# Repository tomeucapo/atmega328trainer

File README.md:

# ATmega328P Weather Station

Firmware and KiCad designs for an ATmega328P weather station and its battery-powered LoRa sensor nodes. The master reads local wind, rain and temperature sensors, displays measurements on an OLED, stores records in I²C EEPROM, and receives remote BME280 readings over LoRa.

The original trainer board includes an optocoupled input for pulse sensors, including 24 V anemometers, and an FT232 USB-to-serial interface.

| Weather station board | IO Expansion board |
| --- | --- |
|  |  |

[PCB project page](https://www.pcbway.com/project/shareproject/Anemometer_with_ATMega128P_fbefd825.html) · [Master schematic (PDF)](schematic/anemometre.pdf) · [IOExtension schematic (PDF)](schematic/IOExtension/IOExtension/IOExtension.pdf) · [Local LoRa/BME280 schematic (PDF)](schematic/lora_bme280_local/lora_bme280_local/lora_bme280_local.pdf)

## Features

- Wind speed from an anemometer and rainfall counting.
- Local temperature from a DS18B20 and indoor temperature, humidity and pressure from a BME280.
- SSD1306 OLED with text and temperature-graph views.
- MCP23017 I/O expander, including an external LED and view button.
- I²C EEPROM logging and weather forecast calculations.
- SX1276/78 LoRa support for up to two remote BME280 nodes.
- Separate firmware target for the low-power remote node.
- Optional BME280 and LoRa devices are detected at startup; if the LoRa module is absent, the master reports it over UART and continues with local functions.

## Hardware

### Master board

| ATmega328P pin | Function |
| --- | --- |
| PB0 | Anemometer input capture (ICP1) |
| PB1 | Rain gauge input (PCINT1) |
| PB2 | DS18B20 1-Wire data; use a 4.7 kΩ pull-up |
| PB3/PB4/PB5 | SPI MOSI/MISO/SCK for the LoRa module |
| PC4/PC5 | I²C SDA/SCL, 100 kHz |
| PD0/PD1 | UART RX/TX, shared with the onboard FT232 |
| PD2/PD3 | LoRa chip select/reset |
| PD6 | Status LED |

The I²C bus is shared by the MCP23017 (`0x20`), SSD1306 (`0x3C`), EEPROM (`0x54`) and BME280 (`0x76`). PB2 is also the ATmega328P SPI `SS` pin, so the firmware suspends SPI while it communicates with the DS18B20 and restores SPI master mode afterward.

The master MCU operates at 8 MHz. The RFM95W/Ra-02 LoRa module is a **3.3 V device**; use a suitable 3.3 V regulator and level shifting between it and a 5 V MCU. Keep the module's chip-select pulled high so ISP programming does not select the radio.

### LoRa remote node

The remote uses an ATmega328P at 3.3 V / 8 MHz, a BME280 and an SX127x radio. It transmits approximately every 64 seconds and sleeps between transmissions. Build node 1 by default; node 2 starts with a 32-second offset to reduce collisions. The master marks a node offline after 180 seconds without a packet.

For remote battery measurement, connect VIN to PC0/ADC0 through a divider: VIN—470 kΩ—PC0—330 kΩ—GND, with 100 nF from PC0 to GND. PC0 is not connected on the current remote PCB, so the divider must be wired to the ATmega328P pin 23. The reported voltage assumes a 3.3 V ADC reference and these resistor values; calibrate for best accuracy.

## Build

Install CMake and the AVR toolchain (`gcc-avr`, `avr-libc`; `binutils-avr` may be a separate package on your system). The master and remote are separate CMake projects.

### Master firmware

From the repository root:

```sh
cmake -S src -B src/build
cmake --build src/build
```

The build creates `src/build/firmware.elf` and `src/build/firmware.hex`. If CMake cached a host compiler instead of `avr-gcc`, use a fresh build directory and configure again.

### LoRa remote firmware

```sh
cmake -S src/lora_remote -B src/lora_remote/build
cmake --build src/lora_remote/build
```

To build node 2, use a separate build directory:

```sh
cmake -S src/lora_remote -B src/lora_remote/build_node2 -DLORA_NODE_ID=2
cmake --build src/lora_remote/build_node2
```

The remote's optional UART diagnostics are disabled by default. Enable them with `-DLORA_DEBUG_UART=ON` in a separate build directory; output is 9600 baud, 8N1, on PD1/TXD and uses 3.3 V logic levels.

```sh
cmake -S src/lora_remote -B src/lora_remote/build_debug -DLORA_DEBUG_UART=ON
cmake --build src/lora_remote/build_debug
```

The remote build creates `firmware_remote.elf` and `firmware_remote.hex` in its selected build directory. For UART diagnostics, connect a 3.3 V USB-to-serial adapter's RX to PD1/TXD and connect GND; the remote only transmits debug output.

Both projects provide a `flash` target that invokes `avrdude` with the `dragon_isp` programmer. Select the appropriate build directory and connect the programmer before running it:

```sh
cmake --build src/build --target flash
cmake --build src/lora_remote/build --target flash
```

## Master serial interface

The master UART is 9600 baud, 8N1 on PD0/PD1, exposed through the onboard FT232. Commands are terminated by CR or LF.

| Command | Purpose |
| --- | --- |
| `@GET_ANEMO` | Read wind speed |
| `@GET_RAIN` | Read rain-tip count and rainfall |
| `@RESET_RAIN` | Reset the rain counter |
| `@GET_TEMP` | Read the DS18B20 temperature |
| `@GET_BME` | Read the latest indoor BME280 data |
| `@GET_EXT` | Read remote node 1 status (alias for `@GET_EXT1`) |
| `@GET_EXT1`, `@GET_EXT2` | Read the selected remote node status |
| `@VIEW` | Toggle OLED text/graph view |
| `@DUMP` | Dump logged EEPROM records |
| `@FORECAST` | Print the current forecast |
| `@MCP_ON <pin>`, `@MCP_OFF <pin>` | Set an MCP23017 output; use `A0`–`A6` or `B0`–`B7` (port A is the default) |

The OLED text view shows both the exterior DS18B20 and indoor BME280 temperatures. `src/test.py` is an older host-side script and still uses legacy `@STAT_*` command names.

## Repository layout

- `src/weatherstation/` — master firmware and shared sensor, display, I²C, SPI, EEPROM and LoRa drivers.
- `src/lora_remote/` — battery-powered remote-node firmware.
- `schematic/` — KiCad schematics and PCB designs for the master and LoRa nodes.

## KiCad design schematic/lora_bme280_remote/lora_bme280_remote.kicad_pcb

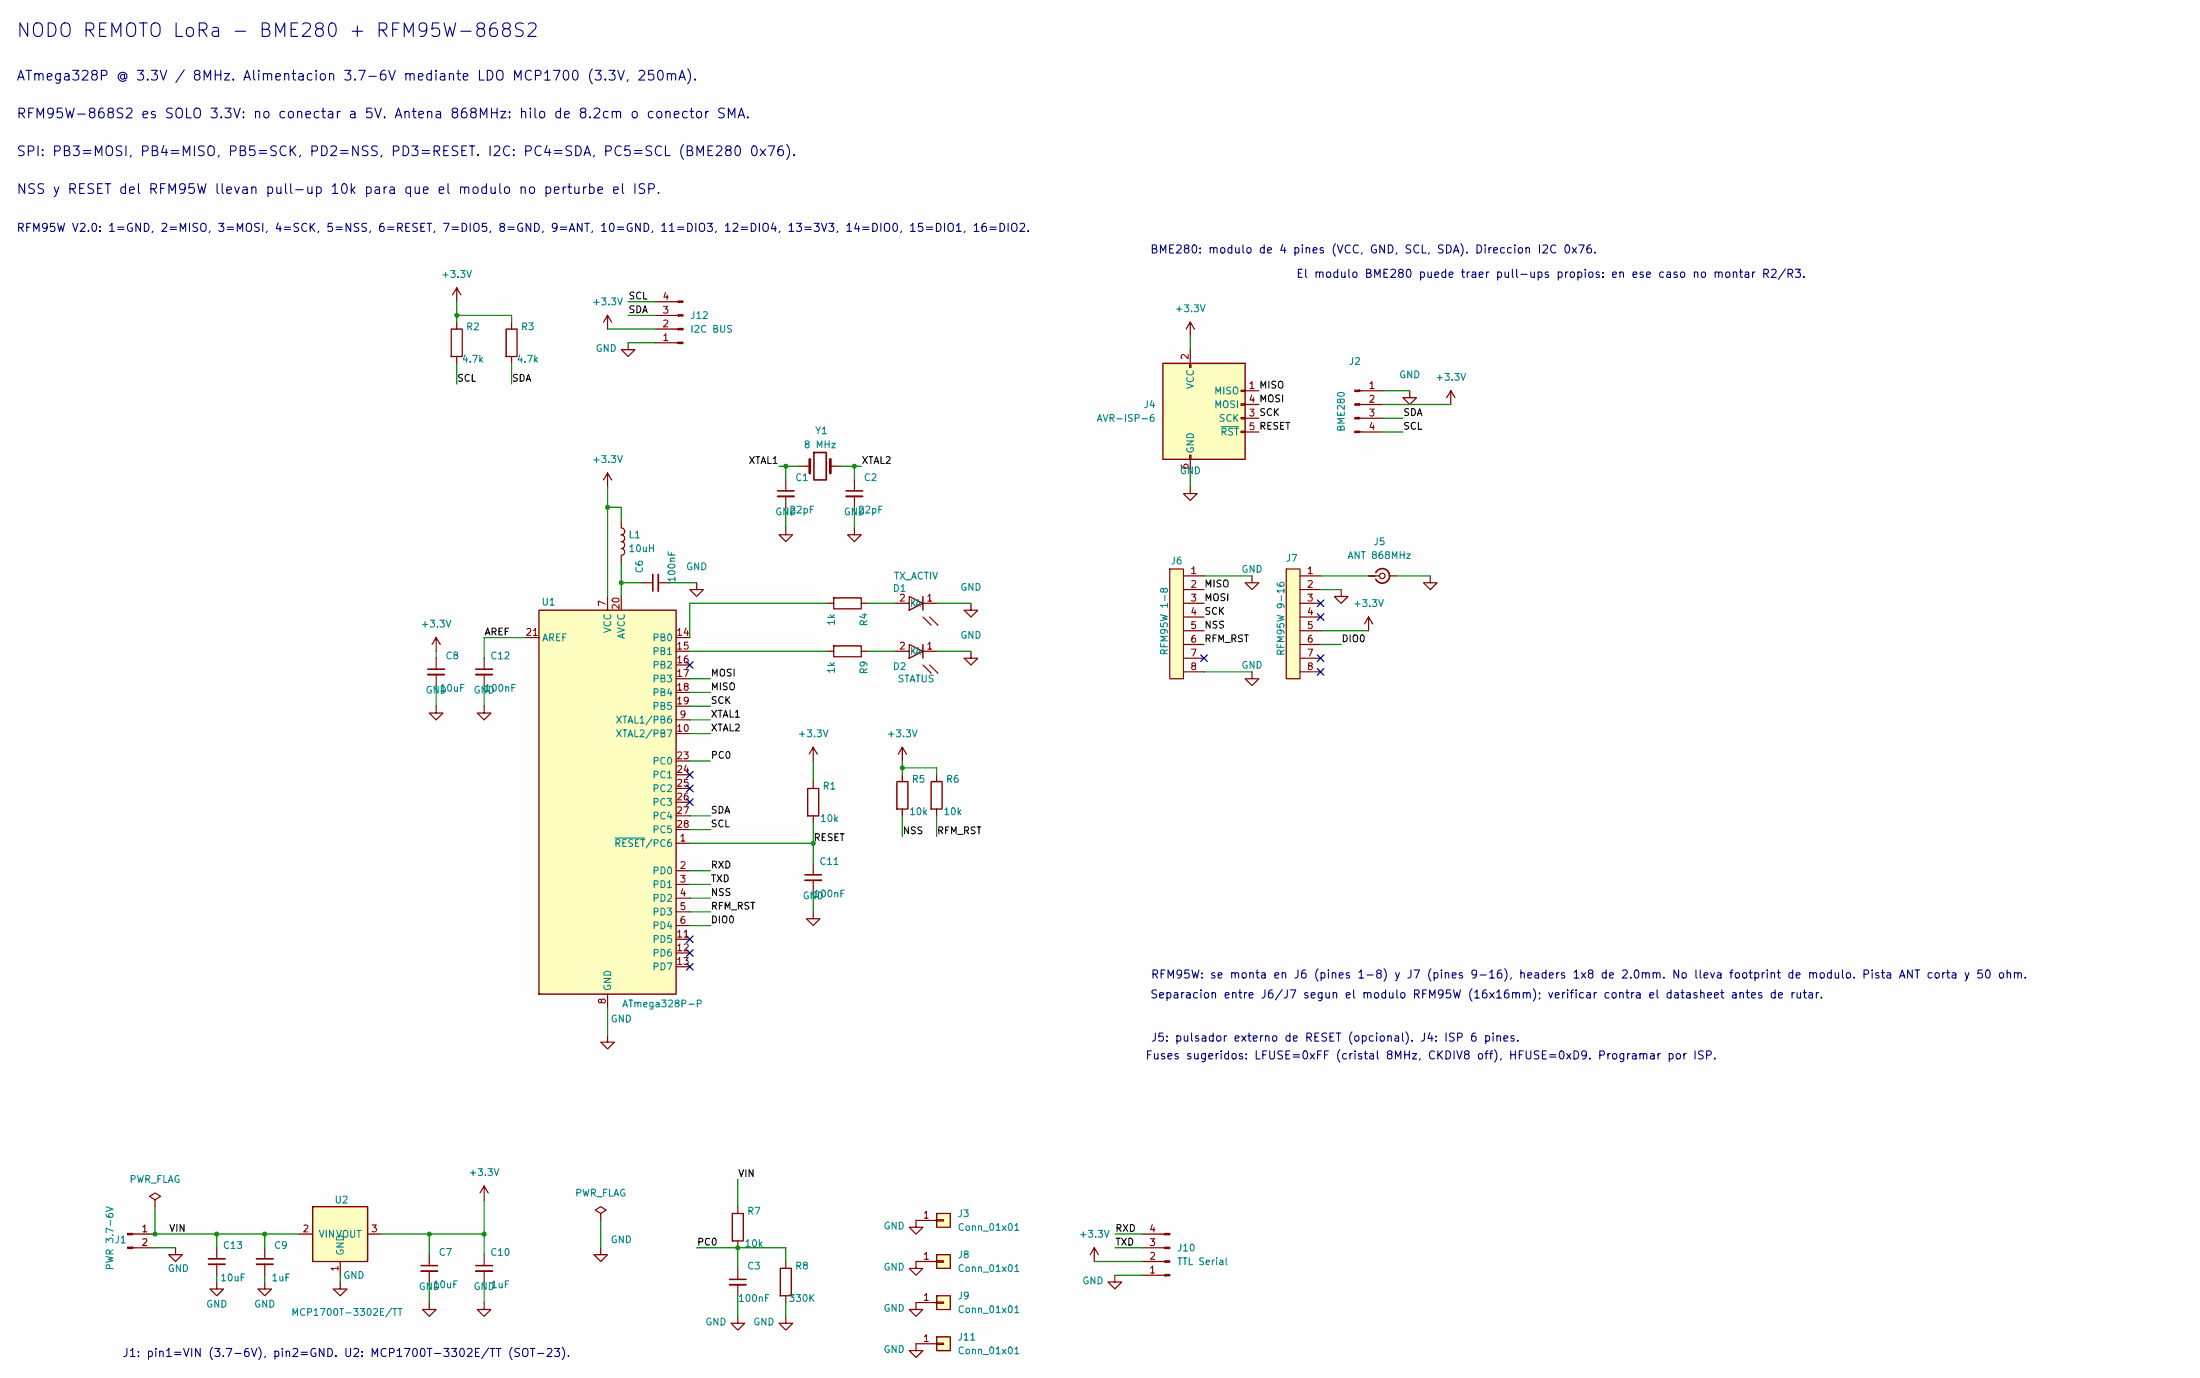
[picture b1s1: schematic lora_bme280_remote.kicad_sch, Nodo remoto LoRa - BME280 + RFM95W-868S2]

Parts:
C1, C2: 22pF; C_Disc_D4.3mm_W1.9mm_P5.00mm
C3, C6, C11, C12: 100nF; C_Disc_D7.0mm_W2.5mm_P5.00mm
C7, C13: 10uF; C_0805_2012Metric
C8: 10uF; C_Disc_D7.0mm_W2.5mm_P5.00mm
C9, C10: 1uF; C_0805_2012Metric
D1: TX_ACTIV; LED_D3.0mm
D2: STATUS; LED_D3.0mm
J1: PWR 3.7-6V; JST_EH_B2B-EH-A_1x02_P2.50mm_Vertical
J2: BME280; PinHeader_1x04_P2.00mm_Vertical
J3, J8, J9, J11: Conn_01x01; MountingHole_3mm_Pad
J4: AVR-ISP-6; IDC-Header_2x03_P2.54mm_Vertical; MPN 75869-131LF; Farnell 2293757
J5: ANT 868MHz; SMA_Amphenol_132134_Vertical
J6: RFM95W 1-8; PinHeader_1x08_P2.00mm_Vertical
J7: RFM95W 9-16; PinHeader_1x08_P2.00mm_Vertical
J10: TTL Serial; PinHeader_1x04_P2.54mm_Vertical
J12: I2C BUS; PinHeader_1x04_P2.54mm_Vertical
L1: 10uH; L_Axial_L5.3mm_D2.2mm_P10.16mm_Horizontal_Vishay_IM-1; MPN 77F100K-TR-RC; Farnell 2924990
R1, R5, R6, R7: 10k; R_Axial_DIN0204_L3.6mm_D1.6mm_P7.62mm_Horizontal
R2, R3: 4.7k; R_Axial_DIN0204_L3.6mm_D1.6mm_P7.62mm_Horizontal
R4, R9: 1k; R_Axial_DIN0204_L3.6mm_D1.6mm_P7.62mm_Horizontal
R8: 330K; R_Axial_DIN0204_L3.6mm_D1.6mm_P7.62mm_Horizontal
U1: ATmega328P-P; DIP-28_W7.62mm; MPN ATMEGA328P-PU; Farnell 1715487
U2: MCP1700T-3302E/TT; SOT-23
Y1: 8 MHz; Crystal_HC49-U_Vertical

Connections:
+3.3V: C7.1, C8.1, C10.1, J2.2, J4.2 (VCC), J7.5, J10.2, J12.2, L1.1, R1.1, R2.1, R3.1, R5.1, R6.1, U1.7 (VCC), U2.3 (VOUT)
/AREF: C12.1, U1.21 (AREF)
/DIO0: J7.6, U1.6 (PD4)
/MISO: J4.1 (MISO), J6.2, U1.18 (PB4)
/MOSI: J4.4 (MOSI), J6.3, U1.17 (PB3)
/NSS: J6.5, R5.2, U1.4 (PD2)
/PC0: C3.1, R7.2, R8.1, U1.23 (PC0)
/RESET: C11.1, J4.5 (~RST), R1.2, U1.1 (~RESET/PC6)
/RFM_RST: J6.6, R6.2, U1.5 (PD3)
/RXD: J10.4, U1.2 (PD0)
/SCK: J4.3 (SCK), J6.4, U1.19 (PB5)
/SCL: J2.4, J12.4, R2.2, U1.28 (PC5)
/SDA: J2.3, J12.3, R3.2, U1.27 (PC4)
/TXD: J10.3, U1.3 (PD1)
/VIN: C9.1, C13.1, J1.1, R7.1, U2.2 (VIN)
/XTAL1: C1.1, U1.9 (XTAL1/PB6), Y1.1
/XTAL2: C2.1, U1.10 (XTAL2/PB7), Y1.2
GND: C1.2, C2.2, C3.2, C6.2, C7.2, C8.2, C9.2, C10.2, C11.2, C12.2, C13.2, D1.1 (K), D2.1 (K), J1.2, J2.1, J3.1, J4.6 (GND), J5.2 (Ext), J6.1, J6.8, J7.2, J8.1, J9.1, J10.1, J11.1, J12.1, R8.2, U1.8 (GND), U1.22 (GND), U2.1 (GND)
unnamed: D1.2 (A), R4.1
unnamed: D2.2 (A), R9.1
unnamed: J5.1 (In), J7.1
unnamed: C6.1, L1.2, U1.20 (AVCC)
unnamed: R4.2, U1.14 (PB0)
unnamed: R9.2, U1.15 (PB1)

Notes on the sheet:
ATmega328P @ 3.3V / 8MHz. Alimentacion 3.7-6V mediante LDO MCP1700 (3.3V, 250mA).
RFM95W-868S2 es SOLO 3.3V: no conectar a 5V. Antena 868MHz: hilo de 8.2cm o conector SMA.
BME280: modulo de 4 pines (VCC, GND, SCL, SDA). Direccion I2C 0x76.
NODO REMOTO LoRa - BME280 + RFM95W-868S2
RFM95W: se monta en J6 (pines 1-8) y J7 (pines 9-16), headers 1x8 de 2.0mm. No lleva footprint de modulo. Pista ANT corta y 50 ohm.
SPI: PB3=MOSI, PB4=MISO, PB5=SCK, PD2=NSS, PD3=RESET. I2C: PC4=SDA, PC5=SCL (BME280 0x76).
J5: pulsador externo de RESET (opcional). J4: ISP 6 pines.
Separacion entre J6/J7 segun el modulo RFM95W (16x16mm); verificar contra el datasheet antes de rutar.
Fuses sugeridos: LFUSE=0xFF (cristal 8MHz, CKDIV8 off), HFUSE=0xD9. Programar por ISP.
El modulo BME280 puede traer pull-ups propios: en ese caso no montar R2/R3.
J1: pin1=VIN (3.7-6V), pin2=GND. U2: MCP1700T-3302E/TT (SOT-23).
RFM95W V2.0: 1=GND, 2=MISO, 3=MOSI, 4=SCK, 5=NSS, 6=RESET, 7=DIO5, 8=GND, 9=ANT, 10=GND, 11=DIO3, 12=DIO4, 13=3V3, 14=DIO0, 15=DIO1, 16=DIO2.
NSS y RESET del RFM95W llevan pull-up 10k para que el modulo no perturbe el ISP.

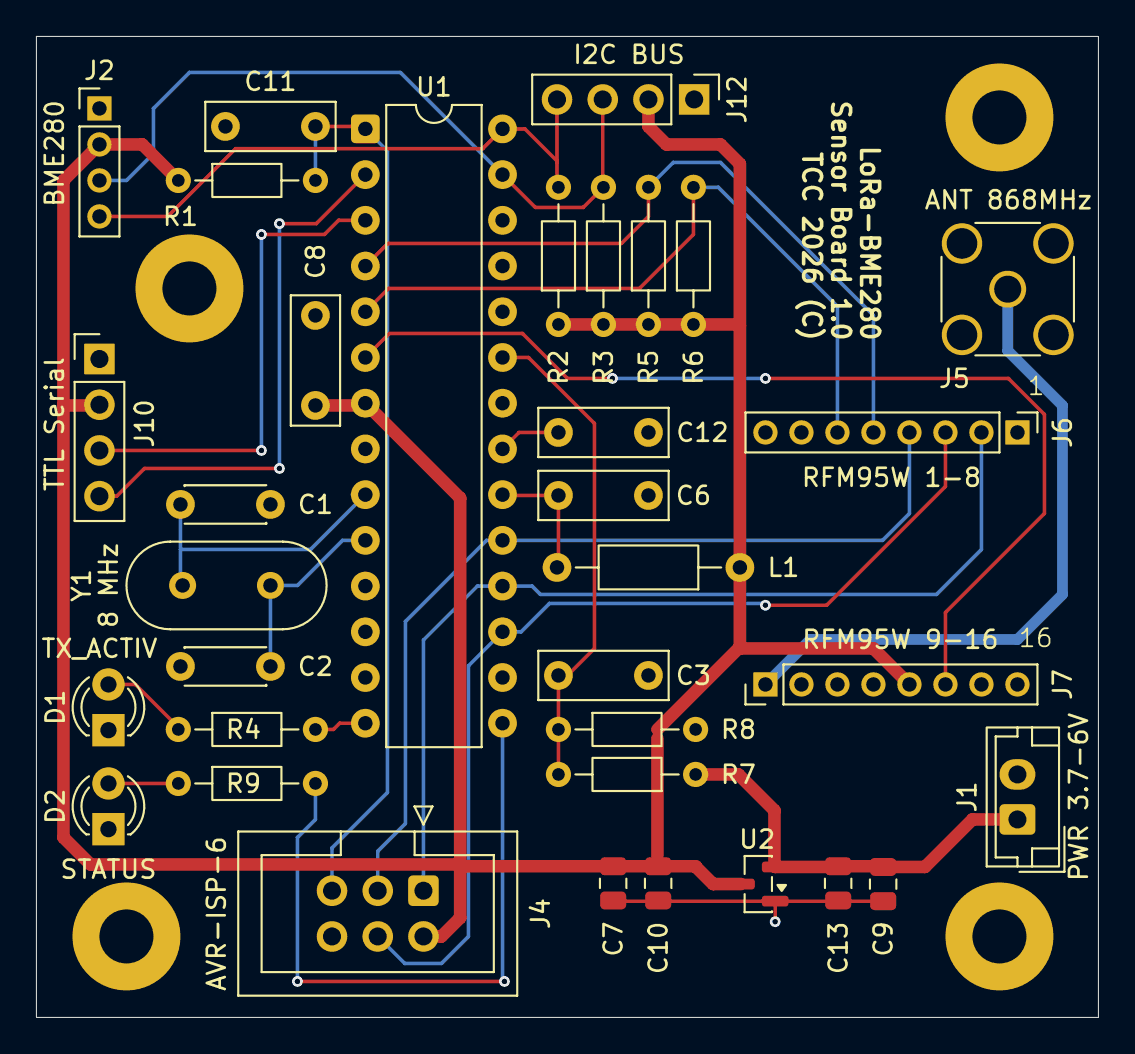
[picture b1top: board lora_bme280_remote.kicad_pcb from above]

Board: 2 copper layers, 59.0 x 54.5 mm, 38 parts (0 on the bottom side), 24 nets.

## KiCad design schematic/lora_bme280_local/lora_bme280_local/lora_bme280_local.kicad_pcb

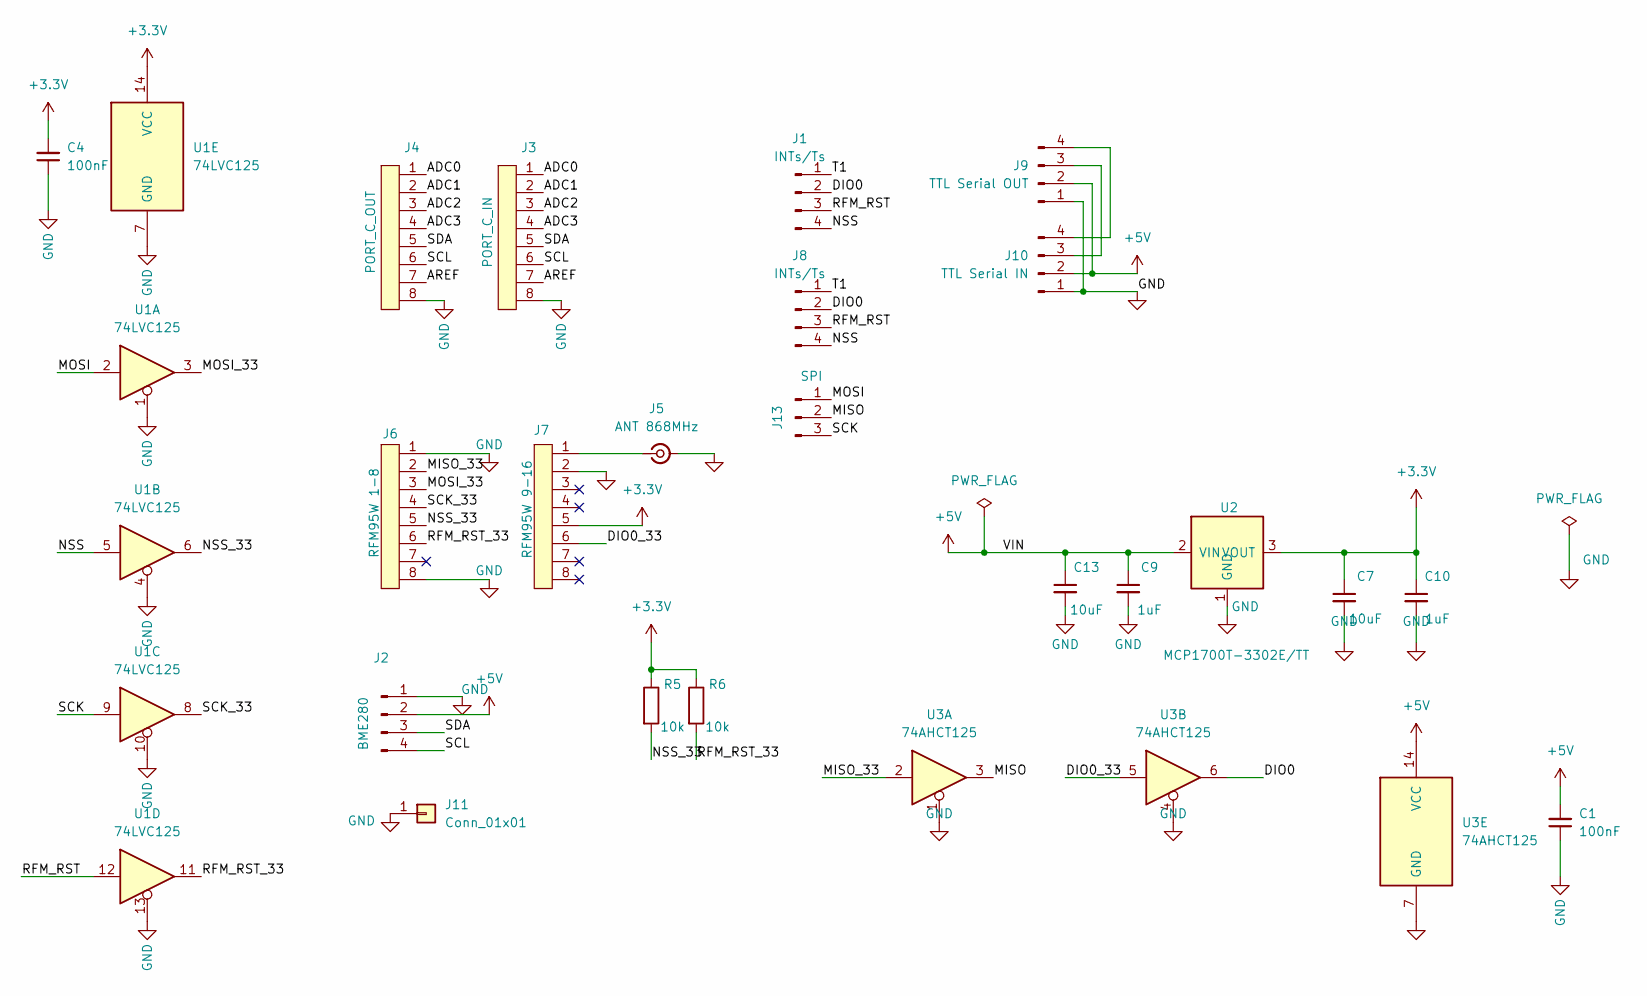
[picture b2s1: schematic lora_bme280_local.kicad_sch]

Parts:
C1: 100nF; C_Disc_D7.0mm_W2.5mm_P5.00mm; MPN CK05BX104K; Farnell 1740547
C4: 100nF; C_0805_2012Metric_Pad1.18x1.45mm_HandSolder; MPN CK05BX104K; Farnell 1740547
C7, C13: 10uF; C_0805_2012Metric
C9, C10: 1uF; C_0805_2012Metric
J1, J8: INTs/Ts; PinHeader_1x04_P2.54mm_Vertical
J2: BME280; JST_PH_B4B-PH-K_1x04_P2.00mm_Vertical
J3: PORT_C_IN; PinHeader_1x08_P2.54mm_Vertical
J4: PORT_C_OUT; PinHeader_1x08_P2.54mm_Vertical
J5: ANT 868MHz; SMA_Amphenol_132134-11_Vertical
J6: RFM95W 1-8; PinHeader_1x08_P2.00mm_Vertical
J7: RFM95W 9-16; PinHeader_1x08_P2.00mm_Vertical
J9: TTL Serial OUT; PinHeader_1x04_P2.54mm_Vertical
J10: TTL Serial IN; PinHeader_1x04_P2.54mm_Vertical
J11: Conn_01x01; MountingHole_3mm_Pad
J13: SPI; PinHeader_1x03_P2.54mm_Vertical
R5, R6: 10k; R_Axial_DIN0204_L3.6mm_D1.6mm_P7.62mm_Horizontal
U1: 74LVC125; TSSOP-14_4.4x5mm_P0.65mm
U2: MCP1700T-3302E/TT; SOT-23
U3: 74AHCT125; DIP-14_W7.62mm

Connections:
+3.3V: C4.2, C7.1, C10.1, J7.5, R5.1, R6.1, U1.14 (VCC), U2.3 (VOUT)
+5V: C1.2, C9.1, C13.1, J2.2, J9.2, J10.2, U2.2 (VIN), U3.14 (VCC)
/ADC0: J3.1, J4.1
/ADC1: J3.2, J4.2
/ADC2: J3.3, J4.3
/ADC3: J3.4, J4.4
/AREF: J3.7, J4.7
/DIO0: J1.2, J8.2, U3.6
/DIO0_33: J7.6, U3.5
/MISO: J13.2, U3.3
/MISO_33: J6.2, U3.2
/MOSI: J13.1, U1.2
/MOSI_33: J6.3, U1.3
/NSS: J1.4, J8.4, U1.5
/NSS_33: J6.5, R5.2, U1.6
/RFM_RST: J1.3, J8.3, U1.12
/RFM_RST_33: J6.6, R6.2, U1.11
/SCK: J13.3, U1.9
/SCK_33: J6.4, U1.8
/SCL: J2.4, J3.6, J4.6
/SDA: J2.3, J3.5, J4.5
/T1: J1.1, J8.1
GND: C1.1, C4.1, C7.2, C9.2, C10.2, C13.2, J2.1, J3.8, J4.8, J5.2 (Ext), J6.1, J6.8, J7.2, J9.1, J10.1, J11.1, U1.1, U1.4, U1.7 (GND), U1.10, U1.13, U2.1 (GND), U3.1, U3.4, U3.7 (GND)
unnamed: J5.1 (In), J7.1
unnamed: J9.3, J10.3
unnamed: J9.4, J10.4

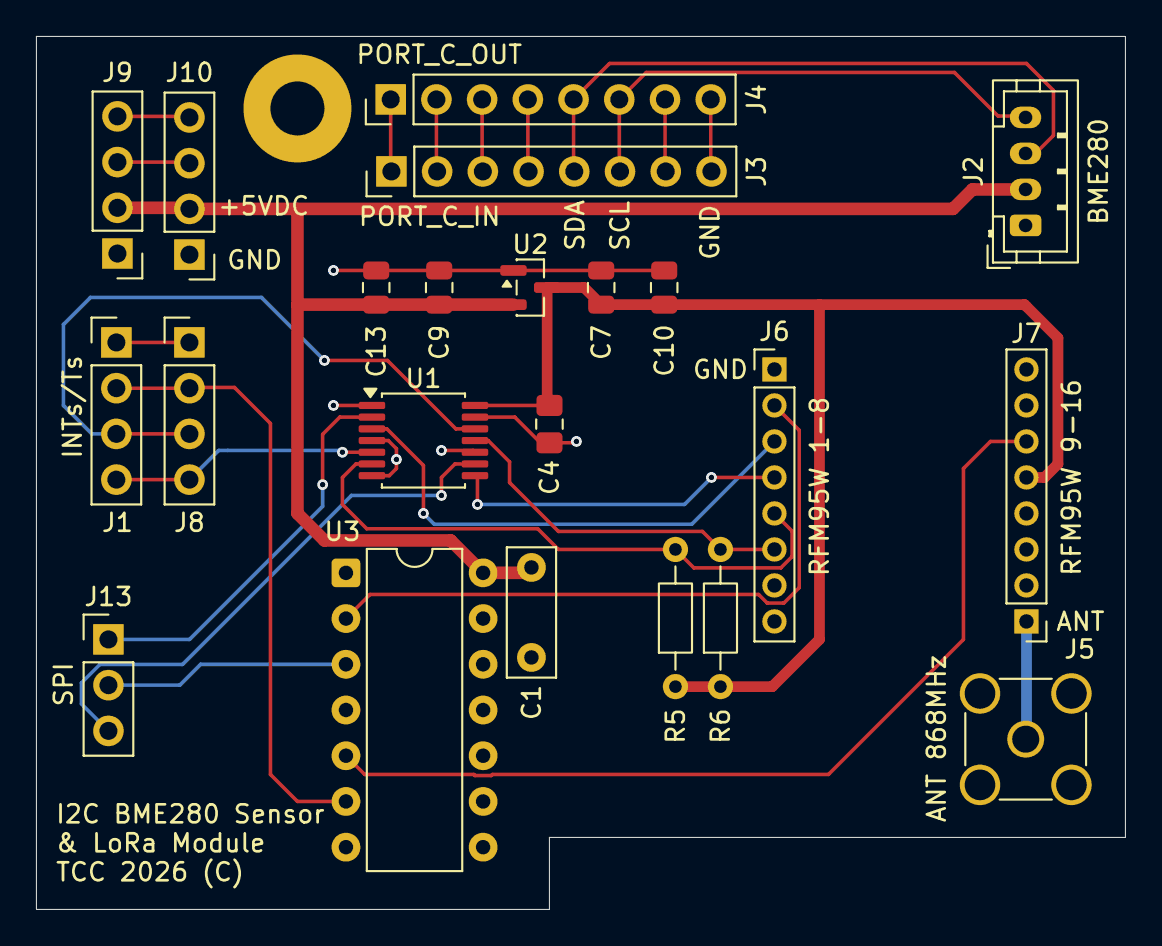
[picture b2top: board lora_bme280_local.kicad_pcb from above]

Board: 2 copper layers, 60.5 x 48.5 mm, 23 parts (0 on the bottom side), 26 nets.

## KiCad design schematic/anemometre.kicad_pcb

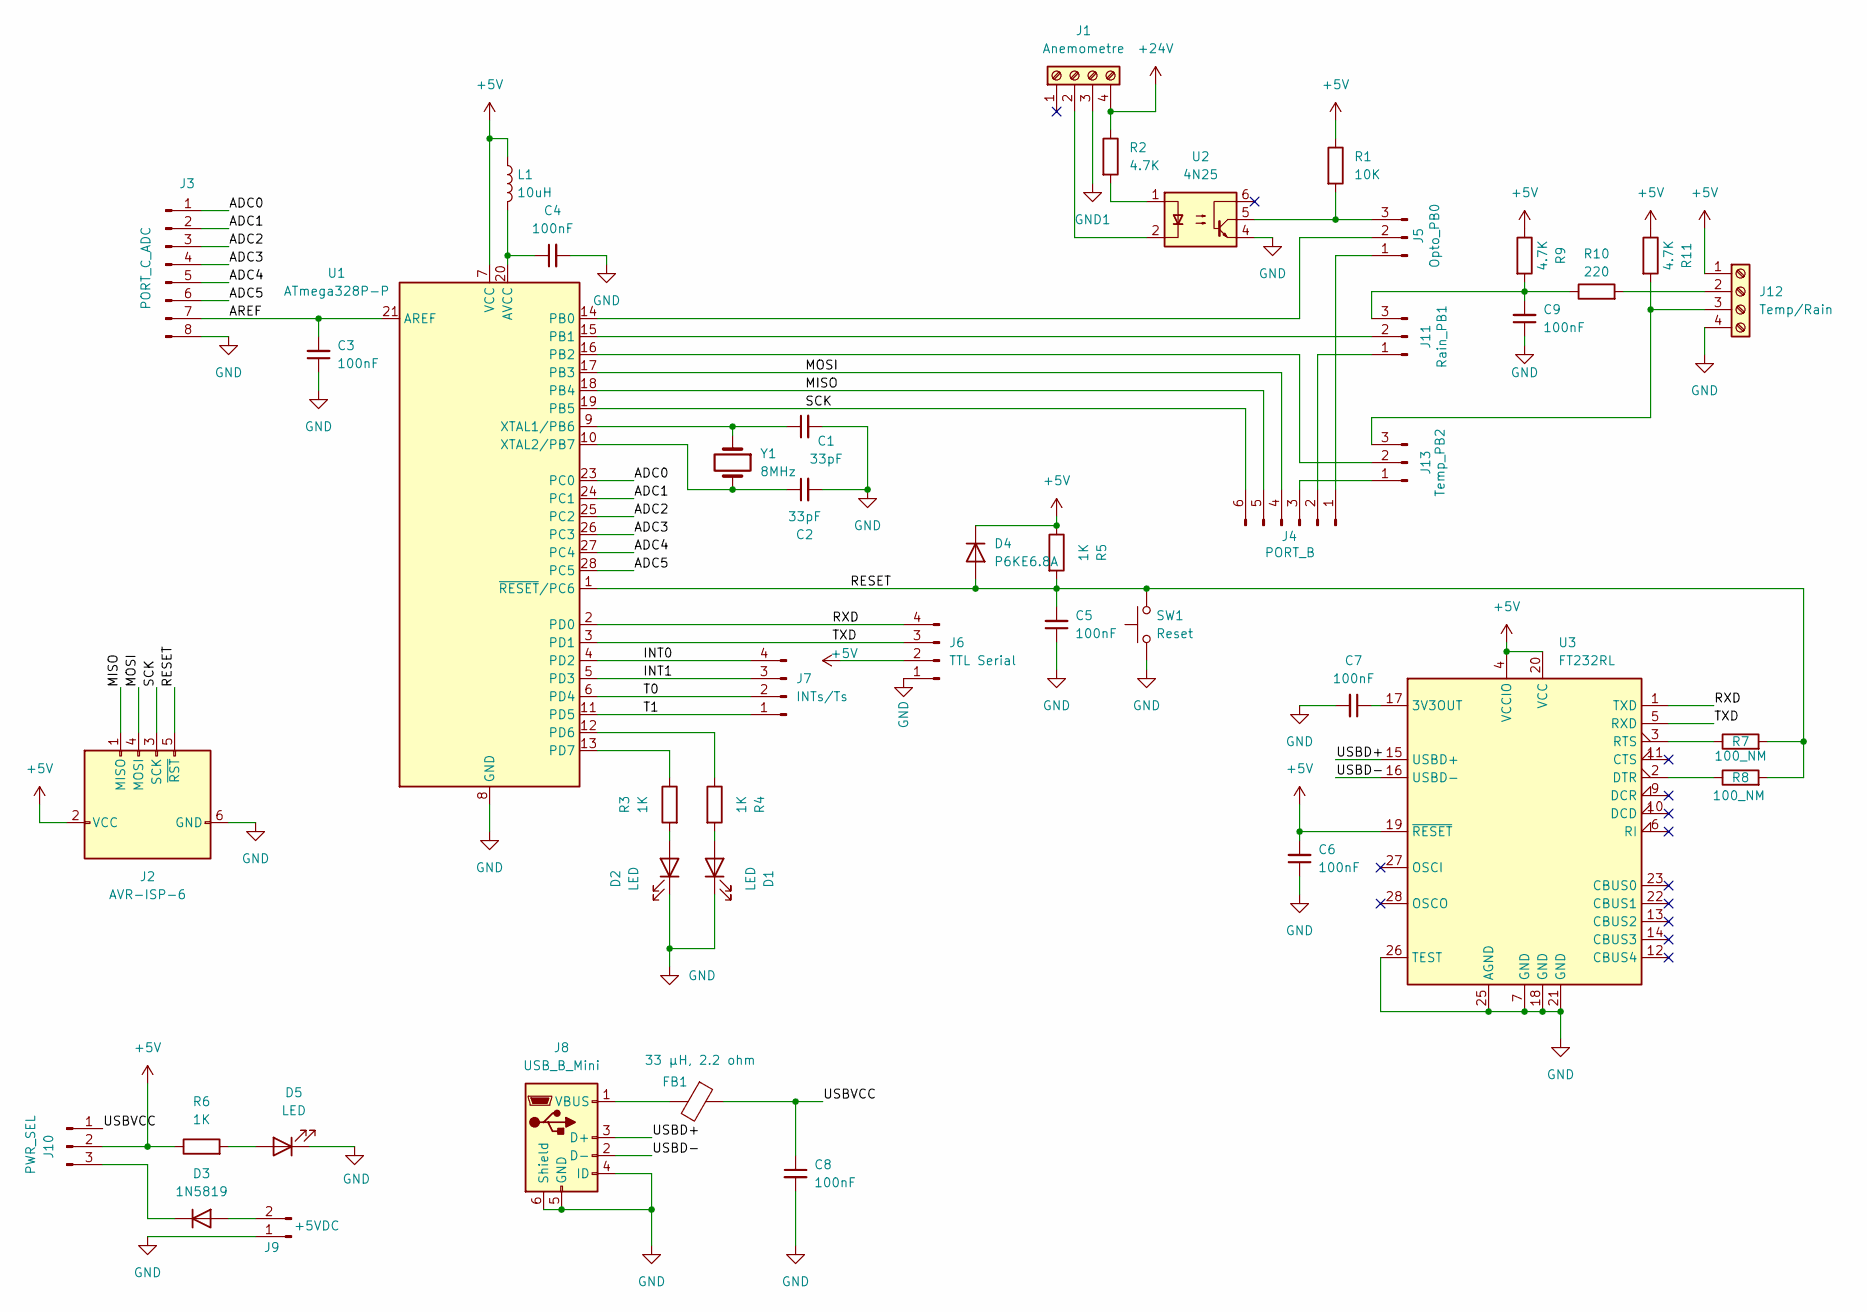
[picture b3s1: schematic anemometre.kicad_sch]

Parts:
C1, C2: 33pF; C_Disc_D4.3mm_W1.9mm_P5.00mm; Farnell 4143719
C3, C4: 100nF; C_Disc_D7.0mm_W2.5mm_P5.00mm; MPN CK05BX104K; Farnell 1740547
C5, C9: 100nF; C_Disc_D7.0mm_W2.5mm_P5.00mm
C6, C7, C8: 100nF; C_0805_2012Metric_Pad1.18x1.45mm_HandSolder; MPN MC0805B104M160CT; Farnell 1708714
D1: LED; LED_D3.0mm; Farnell 2984088
D2: LED; LED_D3.0mm; Farnell 3777906
D3: 1N5819; D_DO-35_SOD27_P10.16mm_Horizontal; MPN 1N5819; Farnell 2677422
D4: P6KE6.8A; D_DO-35_SOD27_P10.16mm_Horizontal; MPN P6KE6.8A; Farnell 3288608
D5: LED; LED_D3.0mm; Farnell 2251291
FB1: 33 µH, 2.2 ohm; L_0805_2012Metric; MPN MLF1608C330KTD25; Farnell 3648165
J1: Anemometre; TerminalBlock_Phoenix_MKDS-1,5-4-5.08_1x04_P5.08mm_Horizont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
J2: AVR-ISP-6; IDC-Header_2x03_P2.54mm_Vertical; MPN 75869-131LF; Farnell 2293757
J3: PORT_C_ADC; PinHeader_1x08_P2.54mm_Vertical
J4: PORT_B; PinHeader_1x06_P2.54mm_Vertical
J5: Opto_PB0; PinHeader_1x03_P2.54mm_Vertical
J6: TTL Serial; PinHeader_1x04_P2.54mm_Vertical
J7: INTs/Ts; PinHeader_1x04_P2.54mm_Vertical
J8: USB_B_Mini; USB_Mini-B_Wuerth_65100516121_Horizontal; MPN 10033526N3212LF; Farnell 2813789
J9: +5VDC; PinHeader_1x02_P2.54mm_Vertical
J10: PWR_SEL; PinHeader_1x03_P2.54mm_Vertical
J11: Rain_PB1; PinHeader_1x03_P2.54mm_Vertical
J12: Temp/Rain; TerminalBlock_Phoenix_MKDS-1,5-4-5.08_1x04_P5.08mm_Horizont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
J13: Temp_PB2; PinHeader_1x03_P2.54mm_Vertical
L1: 10uH; L_Axial_L5.3mm_D2.2mm_P10.16mm_Horizontal_Vishay_IM-1; MPN 77F100K-TR-RC; Farnell 2924990
R1: 10K; R_Axial_DIN0204_L3.6mm_D1.6mm_P7.62mm_Horizontal; Farnell 9339060
R2: 4.7K; R_Axial_DIN0204_L3.6mm_D1.6mm_P7.62mm_Horizontal; Farnell 9339540
R3, R4, R6: 1K; R_Axial_DIN0204_L3.6mm_D1.6mm_P7.62mm_Horizontal; Farnell 9339051
R5: 1K; R_Axial_DIN0204_L3.6mm_D1.6mm_P7.62mm_Horizontal
R7, R8: 100_NM; R_0805_2012Metric_Pad1.20x1.40mm_HandSolder
R9, R11: 4.7K; R_Axial_DIN0204_L3.6mm_D1.6mm_P7.62mm_Horizontal
R10: 220; R_Axial_DIN0204_L3.6mm_D1.6mm_P7.62mm_Horizontal
SW1: Reset; SW_PUSH_6mm_H5mm
U1: ATmega328P-P; DIP-28_W7.62mm; MPN ATMEGA328P-PU; Farnell 1715487
U2: 4N25; DIP-6_W7.62mm; MPN CNY75A; Farnell 1045402
U3: FT232RL; SSOP-28_5.3x10.2mm_P0.65mm; MPN FT232RL-REEL; Farnell 1146032
Y1: 8MHz; Crystal_HC49-U_Vertical; MPN ECS-080-20-4X-DU; Farnell 4076777

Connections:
+5V: C6.2, D4.1 (K), J2.2 (VCC), J6.2, J10.2, J12.1, L1.1, R1.1, R5.1, R6.1, R9.1, R11.1, U1.7 (VCC), U3.4 (VCCIO), U3.19 (~RESET), U3.20 (VCC)
+24V: J1.4, R2.1
/ADC0: J3.1, U1.23 (PC0)
/ADC1: J3.2, U1.24 (PC1)
/ADC2: J3.3, U1.25 (PC2)
/ADC3: J3.4, U1.26 (PC3)
/ADC4: J3.5, U1.27 (PC4)
/ADC5: J3.6, U1.28 (PC5)
/AREF: C3.2, J3.7, U1.21 (AREF)
/INT0: J7.4, U1.4 (PD2)
/INT1: J7.3, U1.5 (PD3)
/MISO: J2.1 (MISO), J4.5, U1.18 (PB4)
/MOSI: J2.4 (MOSI), J4.4, U1.17 (PB3)
/RESET: C5.2, D4.2 (A), J2.5 (~RST), R5.2, R7.2, R8.2, SW1.2, U1.1 (~RESET/PC6)
/RXD: J6.4, U1.2 (PD0), U3.1 (TXD)
/SCK: J2.3 (SCK), J4.6, U1.19 (PB5)
/T0: J7.2, U1.6 (PD4)
/T1: J7.1, U1.11 (PD5)
/TXD: J6.3, U1.3 (PD1), U3.5 (RXD)
/USBD+: J8.3 (D+), U3.15 (USBD+)
/USBD-: J8.2 (D-), U3.16 (USBD-)
/USBVCC: C8.1, FB1.1, J10.1
GND: C1.2, C2.2, C3.1, C4.2, C5.1, C6.1, C7.2, C8.2, C9.1, D1.1 (K), D2.1 (K), D5.1 (K), J2.6 (GND), J3.8, J6.1, J8.4 (ID), J8.5 (GND), J8.6 (Shield), J9.1, J12.4, SW1.1, U1.8 (GND), U1.22 (GND), U2.4, U3.7 (GND), U3.18 (GND), U3.21 (GND), U3.25 (AGND), U3.26 (TEST); also elsewhere on the board
GND1: J1.3
unnamed: D1.2 (A), R4.2
unnamed: D2.2 (A), R3.2
unnamed: D3.2 (A), J9.2
unnamed: D3.1 (K), J10.3
unnamed: D5.2 (A), R6.2
unnamed: J1.2, U2.2
unnamed: J4.1, J5.1
unnamed: J5.2, U1.14 (PB0)
unnamed: J5.3, R1.2, U2.5
unnamed: FB1.2, J8.1 (VBUS)
unnamed: J4.2, J11.1
unnamed: J11.2, U1.15 (PB1)
unnamed: C9.2, J11.3, R9.2, R10.1
unnamed: J12.2, R10.2
unnamed: J12.3, J13.3, R11.2
unnamed: J4.3, J13.1
unnamed: J13.2, U1.16 (PB2)
unnamed: R2.2, U2.1
unnamed: C4.1, L1.2, U1.20 (AVCC)
unnamed: R4.1, U1.12 (PD6)
unnamed: R3.1, U1.13 (PD7)
unnamed: C1.1, U1.9 (XTAL1/PB6), Y1.1
unnamed: C2.1, U1.10 (XTAL2/PB7), Y1.2
unnamed: C7.1, U3.17 (3V3OUT)
unnamed: R8.1, U3.2 (DTR)
unnamed: R7.1, U3.3 (RTS)

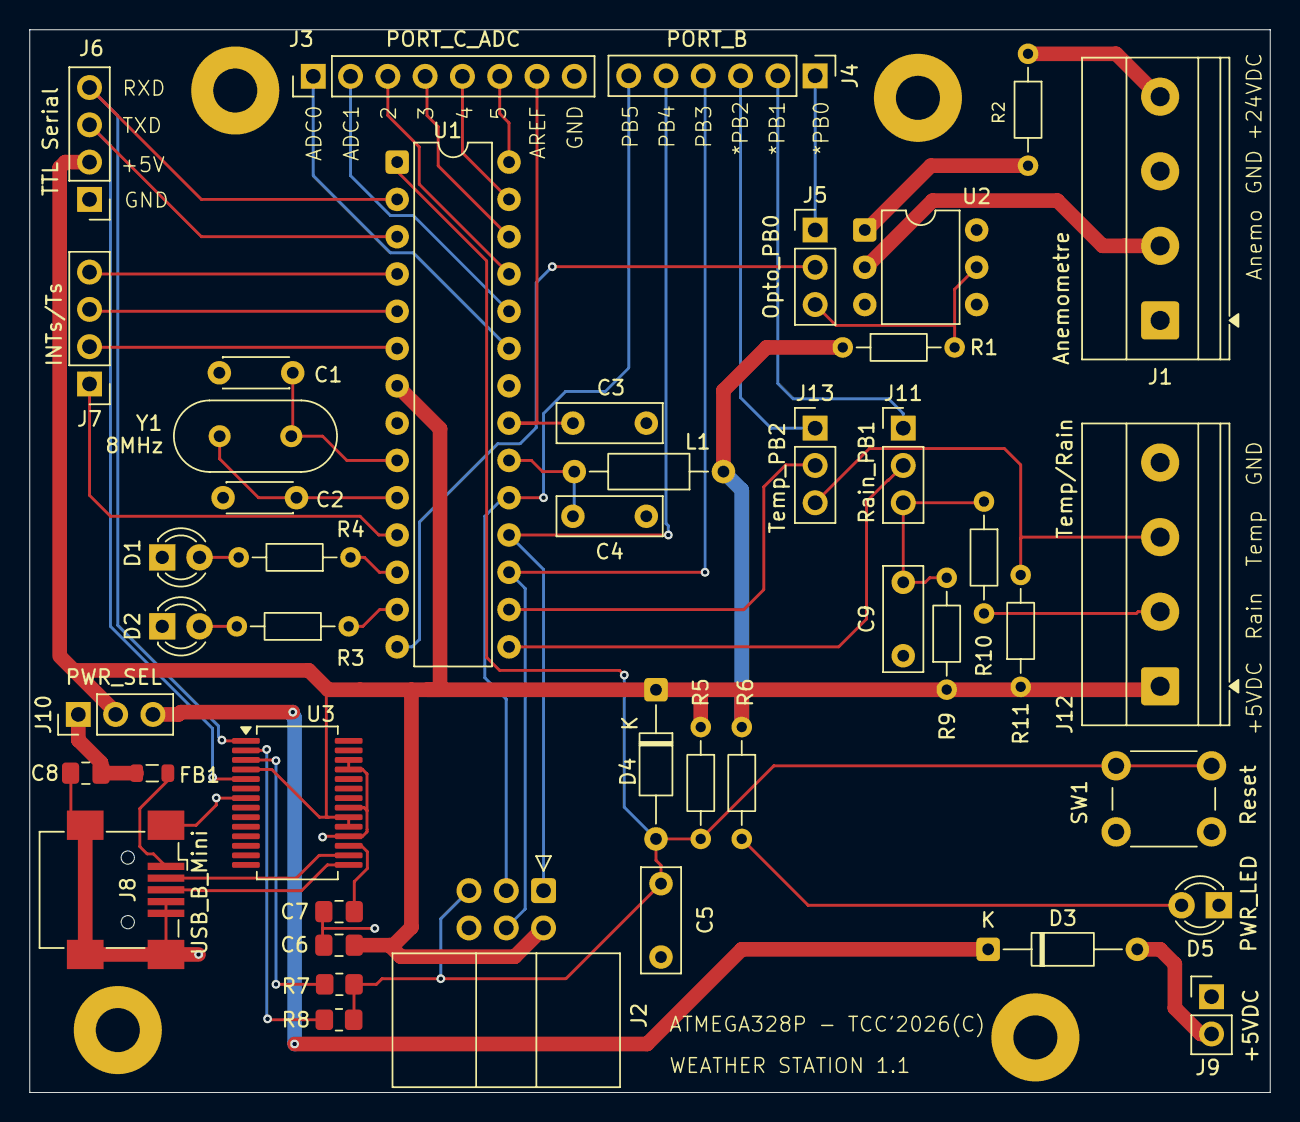
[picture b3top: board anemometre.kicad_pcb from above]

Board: 2 copper layers, 84.5 x 72.4 mm, 49 parts (0 on the bottom side), 49 nets.

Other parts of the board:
J14, J15, J16, J17: Conn_01x01; MountingHole_3mm_Pad

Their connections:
GND: J14.1, J15.1, J16.1, J17.1; also elsewhere on the board

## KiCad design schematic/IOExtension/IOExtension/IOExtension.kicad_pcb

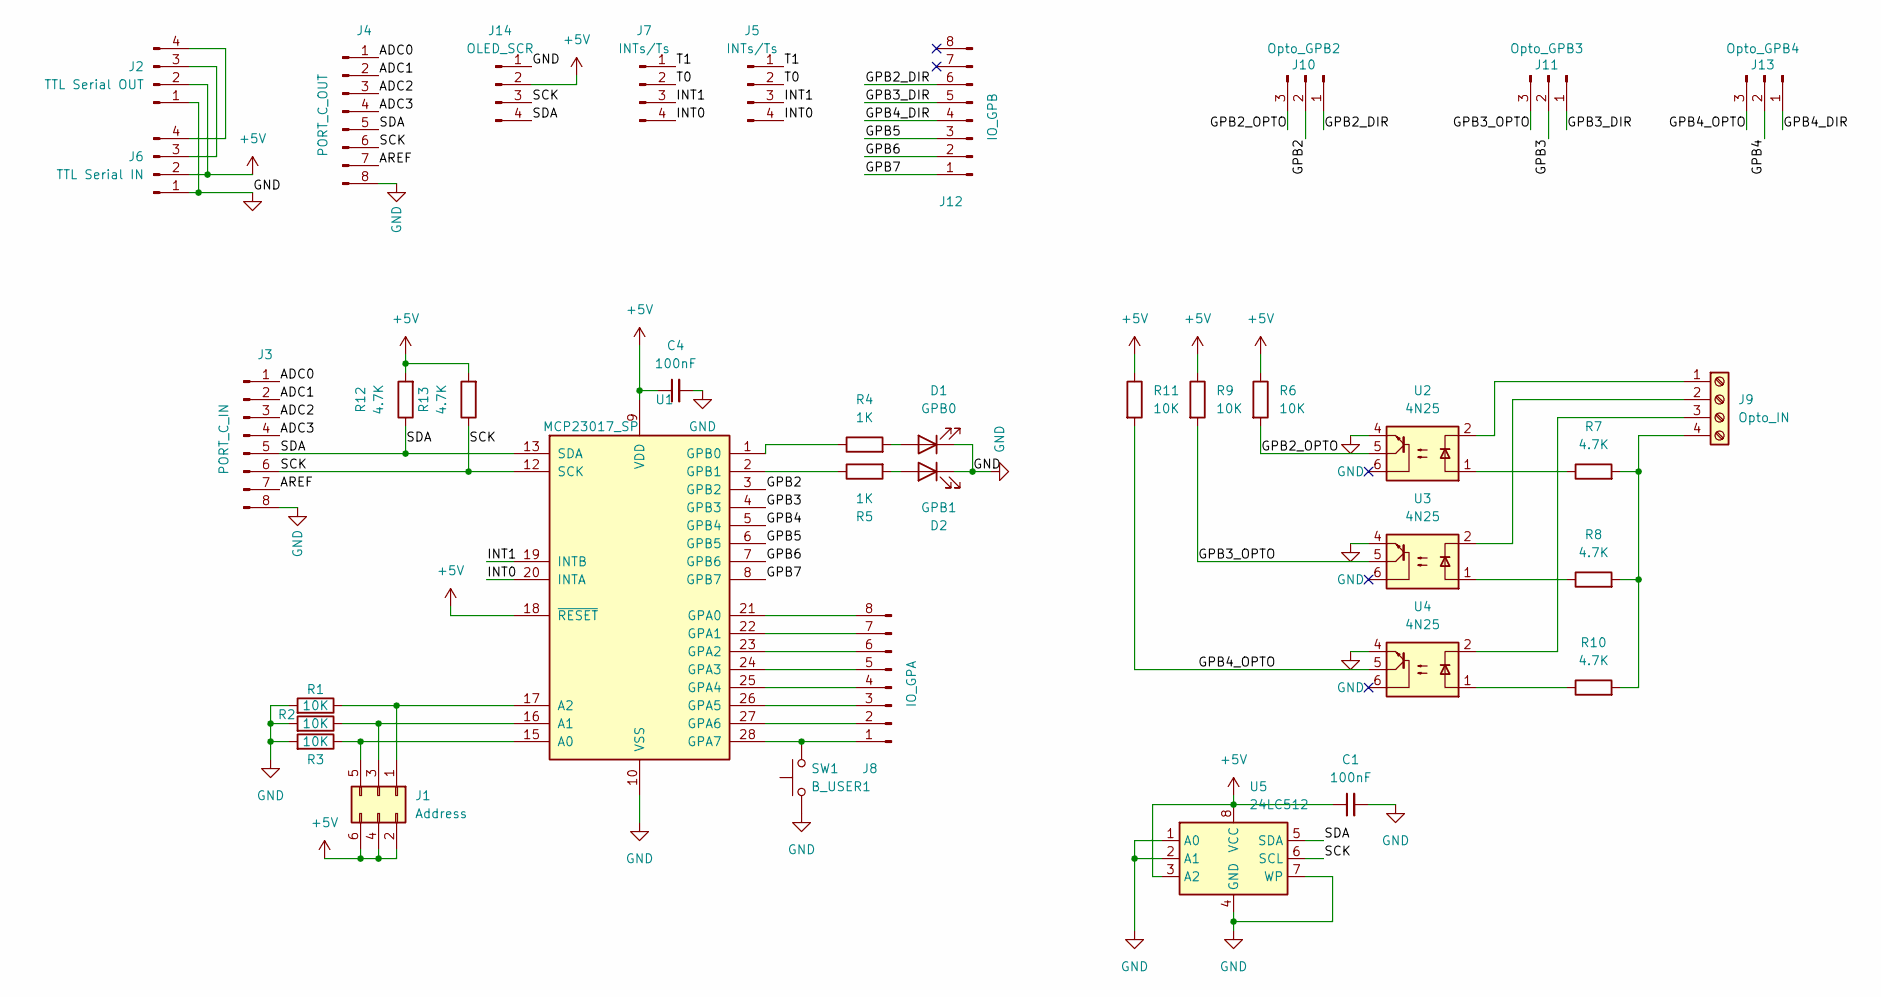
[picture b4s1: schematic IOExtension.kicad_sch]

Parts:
C1, C4: 100nF; C_Disc_D7.0mm_W2.5mm_P5.00mm; MPN CK05BX104K; Farnell 1740547
D1: GPB0; LED_D3.0mm; Farnell 2984088
D2: GPB1; LED_D3.0mm; Farnell 3777906
J1: Address; PinHeader_2x03_P2.54mm_Vertical
J2: TTL Serial OUT; PinHeader_1x04_P2.54mm_Vertical
J3: PORT_C_IN; PinHeader_1x08_P2.54mm_Vertical
J4: PORT_C_OUT; PinHeader_1x08_P2.54mm_Vertical
J5, J7: INTs/Ts; PinHeader_1x04_P2.54mm_Vertical
J6: TTL Serial IN; PinHeader_1x04_P2.54mm_Vertical
J8: IO_GPA; PinHeader_1x08_P2.54mm_Vertical
J9: Opto_IN; TerminalBlock_Phoenix_MKDS-1,5-4-5.08_1x04_P5.08mm_Horizont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
J10: Opto_GPB2; PinHeader_1x03_P2.54mm_Vertical
J11: Opto_GPB3; PinHeader_1x03_P2.54mm_Vertical
J12: IO_GPB; PinHeader_1x08_P2.54mm_Vertical
J13: Opto_GPB4; PinHeader_1x03_P2.54mm_Vertical
J14: OLED_SCR; PinHeader_1x04_P2.54mm_Vertical
R1, R2, R3: 10K; R_Axial_DIN0204_L3.6mm_D1.6mm_P7.62mm_Horizontal; Farnell 9339051
R4, R5: 1K; R_Axial_DIN0204_L3.6mm_D1.6mm_P7.62mm_Horizontal; Farnell 9339051
R6, R9, R11: 10K; R_Axial_DIN0204_L3.6mm_D1.6mm_P7.62mm_Horizontal; Farnell 9339060
R7, R8, R10: 4.7K; R_Axial_DIN0204_L3.6mm_D1.6mm_P7.62mm_Horizontal; Farnell 9339540
R12, R13: 4.7K; R_Axial_DIN0204_L3.6mm_D1.6mm_P7.62mm_Horizontal; Farnell 9339051
SW1: B_USER1; SW_PUSH_6mm_H5mm
U1: MCP23017_SP; DIP-28_W7.62mm
U2, U3, U4: 4N25; DIP-6_W7.62mm; MPN CNY75A; Farnell 1045402
U5: 24LC512; DIP-8_W7.62mm

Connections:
+5V: C1.1, C4.1, J1.2, J1.4, J1.6, J2.2, J6.2, J14.2, R6.1, R9.1, R11.1, R12.2, R13.2, U1.9 (VDD), U1.18 (~RESET), U5.3 (A2), U5.8 (VCC)
/ADC0: J3.1, J4.1
/ADC1: J3.2, J4.2
/ADC2: J3.3, J4.3
/ADC3: J3.4, J4.4
/AREF: J3.7, J4.7
/GPB2: J10.2, U1.3 (GPB2)
/GPB2_DIR: J10.1, J12.6
/GPB2_OPTO: J10.3, R6.2, U2.5
/GPB3: J11.2, U1.4 (GPB3)
/GPB3_DIR: J11.1, J12.5
/GPB3_OPTO: J11.3, R9.2, U3.5
/GPB4: J13.2, U1.5 (GPB4)
/GPB4_DIR: J12.4, J13.1
/GPB4_OPTO: J13.3, R11.2, U4.5
/GPB5: J12.3, U1.6 (GPB5)
/GPB6: J12.2, U1.7 (GPB6)
/GPB7: J12.1, U1.8 (GPB7)
/INT0: J5.4, J7.4, U1.20 (INTA)
/INT1: J5.3, J7.3, U1.19 (INTB)
/SCK: J3.6, J4.6, J14.3, R13.1, U1.12 (SCK), U5.6 (SCL)
/SDA: J3.5, J4.5, J14.4, R12.1, U1.13 (SDA), U5.5 (SDA)
/T0: J5.2, J7.2
/T1: J5.1, J7.1
GND: C1.2, C4.2, D1.1 (K), D2.1 (K), J2.1, J3.8, J4.8, J6.1, J14.1, R1.2, R2.2, R3.2, SW1.1, U1.10 (VSS), U2.4, U3.4, U4.4, U5.1 (A0), U5.2 (A1), U5.4 (GND), U5.7 (WP); also elsewhere on the board
unnamed: D1.2 (A), R4.2
unnamed: D2.2 (A), R5.2
unnamed: J1.1, R1.1, U1.17 (A2)
unnamed: J1.3, R2.1, U1.16 (A1)
unnamed: J1.5, R3.1, U1.15 (A0)
unnamed: J2.3, J6.3
unnamed: J2.4, J6.4
unnamed: J8.1, SW1.2, U1.28 (GPA7)
unnamed: J8.2, U1.27 (GPA6)
unnamed: J8.3, U1.26 (GPA5)
unnamed: J8.4, U1.25 (GPA4)
unnamed: J8.5, U1.24 (GPA3)
unnamed: J8.6, U1.23 (GPA2)
unnamed: J8.7, U1.22 (GPA1)
unnamed: J8.8, U1.21 (GPA0)
unnamed: J9.1, U2.2
unnamed: J9.2, U3.2
unnamed: J9.3, U4.2
unnamed: J9.4, R7.2, R8.2, R10.2
unnamed: R7.1, U2.1
unnamed: R8.1, U3.1
unnamed: R10.1, U4.1
unnamed: R4.1, U1.1 (GPB0)
unnamed: R5.1, U1.2 (GPB1)
